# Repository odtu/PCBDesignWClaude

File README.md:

# PCBDesignWClaude: Inductive Absolute Encoder (branch `inductive-encoder`)

This branch holds a separate KiCad project from `main` (the 3-phase ESC): a contactless **absolute inductive rotary encoder**. It was designed with Claude Code and the PowerLab KiCad Assistant, after TI's **TIDA-010961** reference design ([TIDUFF8](https://www.ti.com/lit/pdf/tiduff8)).

- **Sensing:** dual-track Nonius coils, 16 and 15 periods, in a Ø58 mm coil area. The absolute angle comes from the phase difference between the two tracks.
- **Electronics:** 2 × LDC5072-Q1 inductive front ends, 2 × TLV9062 op-amps, an MSPM0G3507 MCU (both ADCs sample simultaneously) and a REF35330 3.3 V reference.
- **Power and interface:** 12–24 V input to an LMR51610 buck, then the TPS70950 and TPS70933 LDOs. The host connection carries UART at 2.5 Mbaud, SYNC and SWD.
- **Rules and parts:** the design follows the [METU PowerLab PCB design rules](https://github.com/odtu/Powerlab/blob/master/KiCAD/PCB_DESIGN_RULES.md) and uses parts from [PowerLabKiCadLibraries](https://github.com/odtu/PowerLabKiCadLibraries).

## Boards

The stack is the same as TI's: the target, a 0.5 mm air gap, the stator, then the 2×6 board-to-board headers, then the signal board.

| Board | Files | |
|---|---|---|
| Stator (coil board) | `InductiveEncoder.kicad_pro` | Ø76 mm, 4 layers. Generated coils, net ties, J2/J3 male headers on the bottom. No GND copper, so nothing acts as a shorted turn. |
| Signal board | `signal/EncoderSignal.kicad_pro` | Ø76 mm, 4 layers, the same M3 holes. All electronics. J2/J3 sockets on top, J1 host connector on the bottom. |
| Target | `target/EncoderTarget.kicad_pcb` | Ø56 mm, 2 layers, copper segments. It rotates with the shaft. |

## Status

- **Schematics:**
  - Hierarchical, on the PowerLab drawing sheet.
  - ERC: 0 errors.
  - PDFs: [docs/schematic_signal.pdf](docs/schematic_signal.pdf), [docs/schematic_stator.pdf](docs/schematic_stator.pdf).
- **Boards:**
  - DRC on both: 0 errors, 0 unconnected, 0 schematic-parity issues.
  - Remaining warnings: footprint-library mismatches (mask bridges allowed inside the fine-pitch ICs), one J1 silk circle near the edge, one narrow pour neck.
- **Fab outputs** in [fab/](fab/): Gerber and drill zip, BOM, position file and assembly drawings for each board.
- **Routing:**
  - The signal-board routing was reworked after [odtu/PowerLabKiCadAssistant#21](https://github.com/odtu/PowerLabKiCadAssistant/issues/21).
  - The resulting rules are proposed in odtu/Powerlab#147 and odtu/PowerLabKiCadAssistant#22. See "How the signal board was routed" below.

Before ordering:
- Add teardrops (Edit → Edit Teardrops; KiCad has no scripting API for them), then rerun `tools/fab_outputs.py`.
- Set the project number (`${PROJECTNUMBER}` is `TBD` in `tools/lab_setup.py`).
- Replace C4/C5 (22 µF 0603, 10 V) on the 6.1 V rail with 16–25 V parts. At 6.1 V they lose most of their capacitance to DC bias.
- The round boards need a panel for PCBWay assembly.
- There's no reverse-polarity protection: use a keyed cable.
- Firmware isn't part of this project.

## How the signal board was routed

`tools/route_signal.py` runs this chain on the placed board:

1. **`fanout.py`:**
   - **GND:** the pours connect the GND pads. A via goes at the pad only for decoupling caps and fine-pitch IC GND pins. Pads the pour can't reach got a via after routing.
   - **Fine-pitch power pins:** 0.25 mm neck-downs.
   - **Escape lanes:** kept free in front of fine-pitch pins.
2. **`power_route.py`:** the rails come first, at the 0.5 mm Power class width. Freerouting 2.4.1 ignores net-class widths.
3. **`autoroute.py signal`:** Freerouting 2.4.1 (Java 25) routes the signals. GND and the rails are keepouts, and the In1 GND plane is a plane layer.
4. **`maze_route.py`:** a grid A* router finishes what is still open. `ripup.py` frees a congested pin row first when needed.
5. **`track_opt.py`:**
   - Shortcuts detours with 45° segments and chamfers every corner of 90° or less.
   - Ends tracks straight at the pad centre.
   - Removes stubs and duplicates.
   - Widens Power/GND tracks to class width, with a 0.15 mm minimum for everything.

Afterwards, the finishing scripts add the rest:
- `zones.py signal`: the GND pours, slotted at 90° so they don't form a closed ring around the shaft;
- `lab_extras.py`: the stitching vias, the local fiducials at the MCU and the J1 labels;
- `silk.py` and `board_info.py`: the silkscreen and the board info.

The whole regeneration sequence, from coils and schematics to fab outputs, is in [docs/DESIGN_NOTES.md](docs/DESIGN_NOTES.md#regenerating).

## Repository layout

```
InductiveEncoder.kicad_*      stator project (root sheet + coils.kicad_sch)
signal/                       signal-board project (7 sheets)
target/                       target disc
tools/                        Python generators and layout/routing scripts (KiCad 10 python / system python)
fab/<board>/                  ordering files (Gerber+drill zip, BOM, pos, assembly PDFs)
docs/                         schematic PDFs, views, design notes
METUPowerLab_KiCadSchematicTemplate.kicad_wks   lab drawing sheet (also in signal/)
```

## Opening and regenerating

- **KiCad 10.**
  - The schematics and boards carry embedded copies of every symbol and footprint, so the project opens without extra libraries.
  - The new parts are in [odtu/PowerLabKiCadLibraries#13](https://github.com/odtu/PowerLabKiCadLibraries/pull/13): LDC5072, MSPM0G3507, TLV9062, REF35330, TPS709xx, the 2×6 header and socket, and some passives. That PR is not merged yet.
- **Generated files:** the `.kicad_sch` files are generated by `tools/encoder_circuit.py`, and the stator coils by `tools/coilgen.py`. Edit the scripts, not the generated sheets.
- **Tool paths:** some scripts have local paths you'll need to change on another machine:
  - the KiCad install, `C:/Program Files/KiCad/10.0`;
  - the PowerLab library and Assistant folders, used for logos, fiducials, Java 25 and Freerouting.

## License

See [license.txt](license.txt) (same as `main`).

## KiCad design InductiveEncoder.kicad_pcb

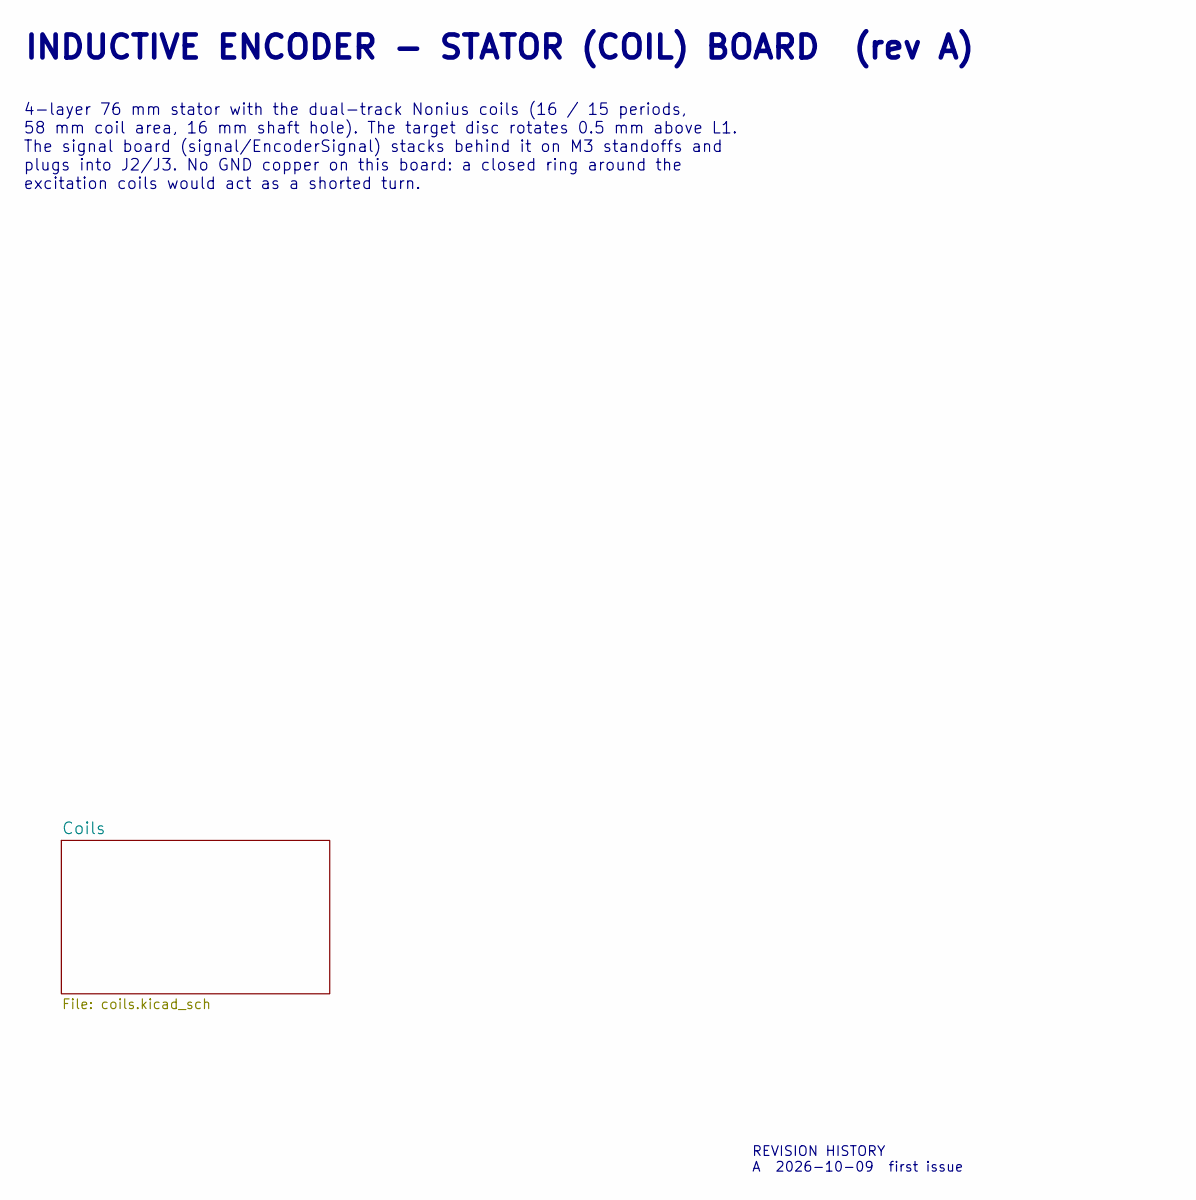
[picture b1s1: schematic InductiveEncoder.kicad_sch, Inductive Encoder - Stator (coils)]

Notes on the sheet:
INDUCTIVE ENCODER - STATOR (COIL) BOARD (rev A)
4-layer 76 mm stator with the dual-track Nonius coils (16 / 15 periods, 58 mm coil area, 16 mm shaft hole). The target disc rotates 0.5 mm above L1. The signal board (signal/EncoderSignal) stacks behind it on M3 standoffs and plugs into J2/J3. No GND copper on this board: a closed ring around the e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
REVISION HISTORY A 2026-10-09 first issue

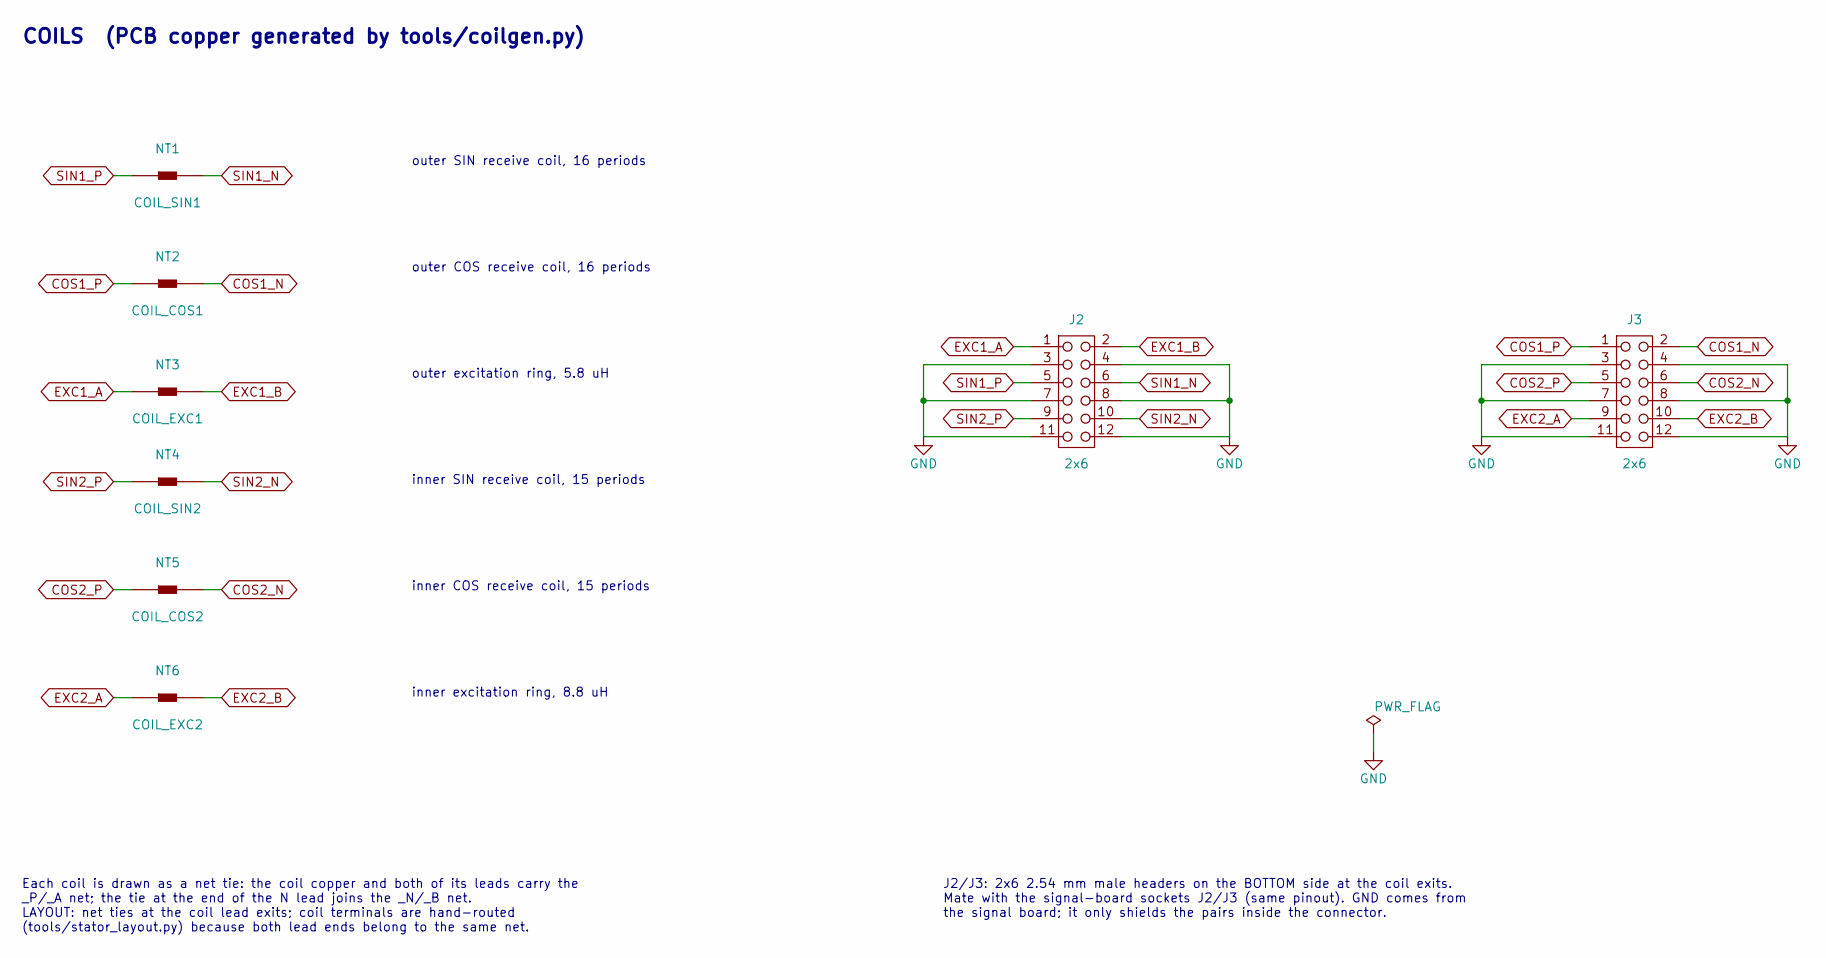
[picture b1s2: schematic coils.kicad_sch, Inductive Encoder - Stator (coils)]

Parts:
J2, J3: 2x6; 61301221121; Current Rating 3A; Voltage Rating 250V; Digi-Key Number 732-5297-ND
NT1: COIL_SIN1; NetTie_2_0.5mm
NT2: COIL_COS1; NetTie_2_0.5mm
NT3: COIL_EXC1; NetTie_2_0.5mm
NT4: COIL_SIN2; NetTie_2_0.5mm
NT5: COIL_COS2; NetTie_2_0.5mm
NT6: COIL_EXC2; NetTie_2_0.5mm

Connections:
COS1_N: J3.2, NT2.2
COS1_P: J3.1, NT2.1
COS2_N: J3.6, NT5.2
COS2_P: J3.5, NT5.1
EXC1_A: J2.1, NT3.1
EXC1_B: J2.2, NT3.2
EXC2_A: J3.9, NT6.1
EXC2_B: J3.10, NT6.2
GND: J2.3, J2.4, J2.7, J2.8, J2.11, J2.12, J3.3, J3.4, J3.7, J3.8, J3.11, J3.12
SIN1_N: J2.6, NT1.2
SIN1_P: J2.5, NT1.1
SIN2_N: J2.10, NT4.2
SIN2_P: J2.9, NT4.1

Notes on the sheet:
COILS (PCB copper generated by tools/coilgen.py)
outer SIN receive coil, 16 periods
outer COS receive coil, 16 periods
outer excitation ring, 5.8 uH
inner SIN receive coil, 15 periods
inner COS receive coil, 15 periods
inner excitation ring, 8.8 uH
Each coil is drawn as a net tie: the coil copper and both of its leads carry the _P/_A net; the tie at the end of the N lead joins the _N/_B net. LAYOUT: net ties at the coil lead exits; coil terminals are hand-routed (tools/stator_layout.py) because both lead ends belong to the same net.
J2/J3: 2x6 2.54 mm male headers on the BOTTOM side at the coil exits. Mate with the signal-board sockets J2/J3 (same pinout). GND comes from the signal board; it only shields the pairs inside the connector.

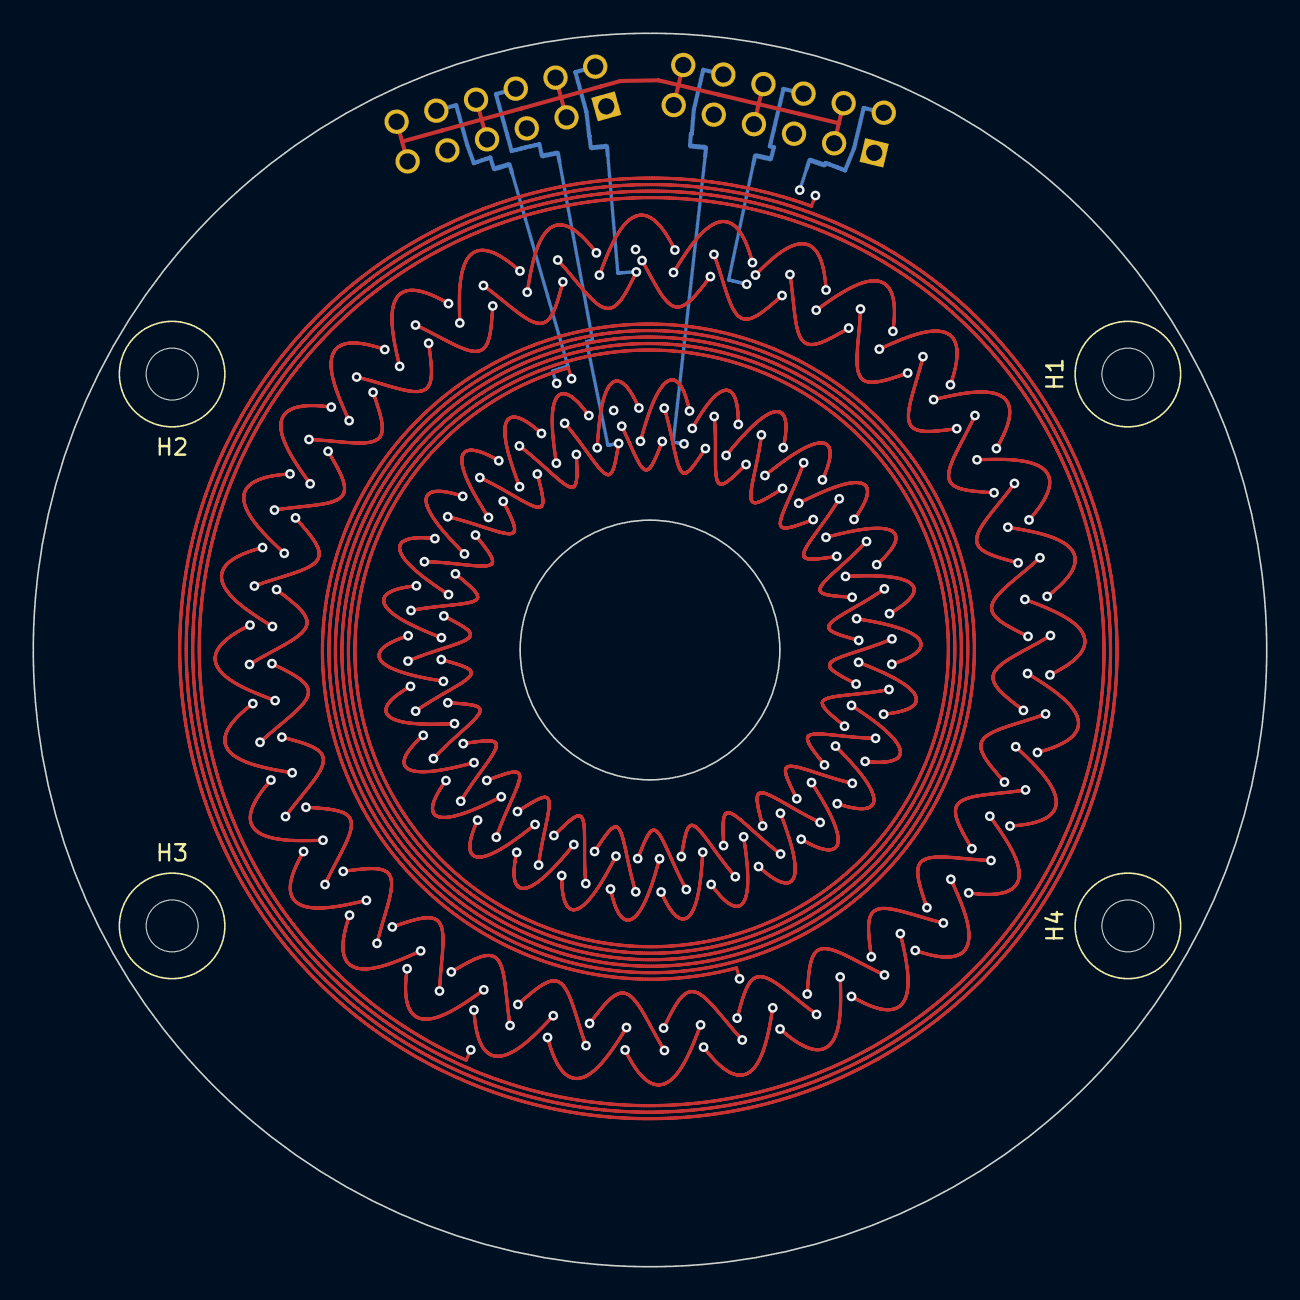
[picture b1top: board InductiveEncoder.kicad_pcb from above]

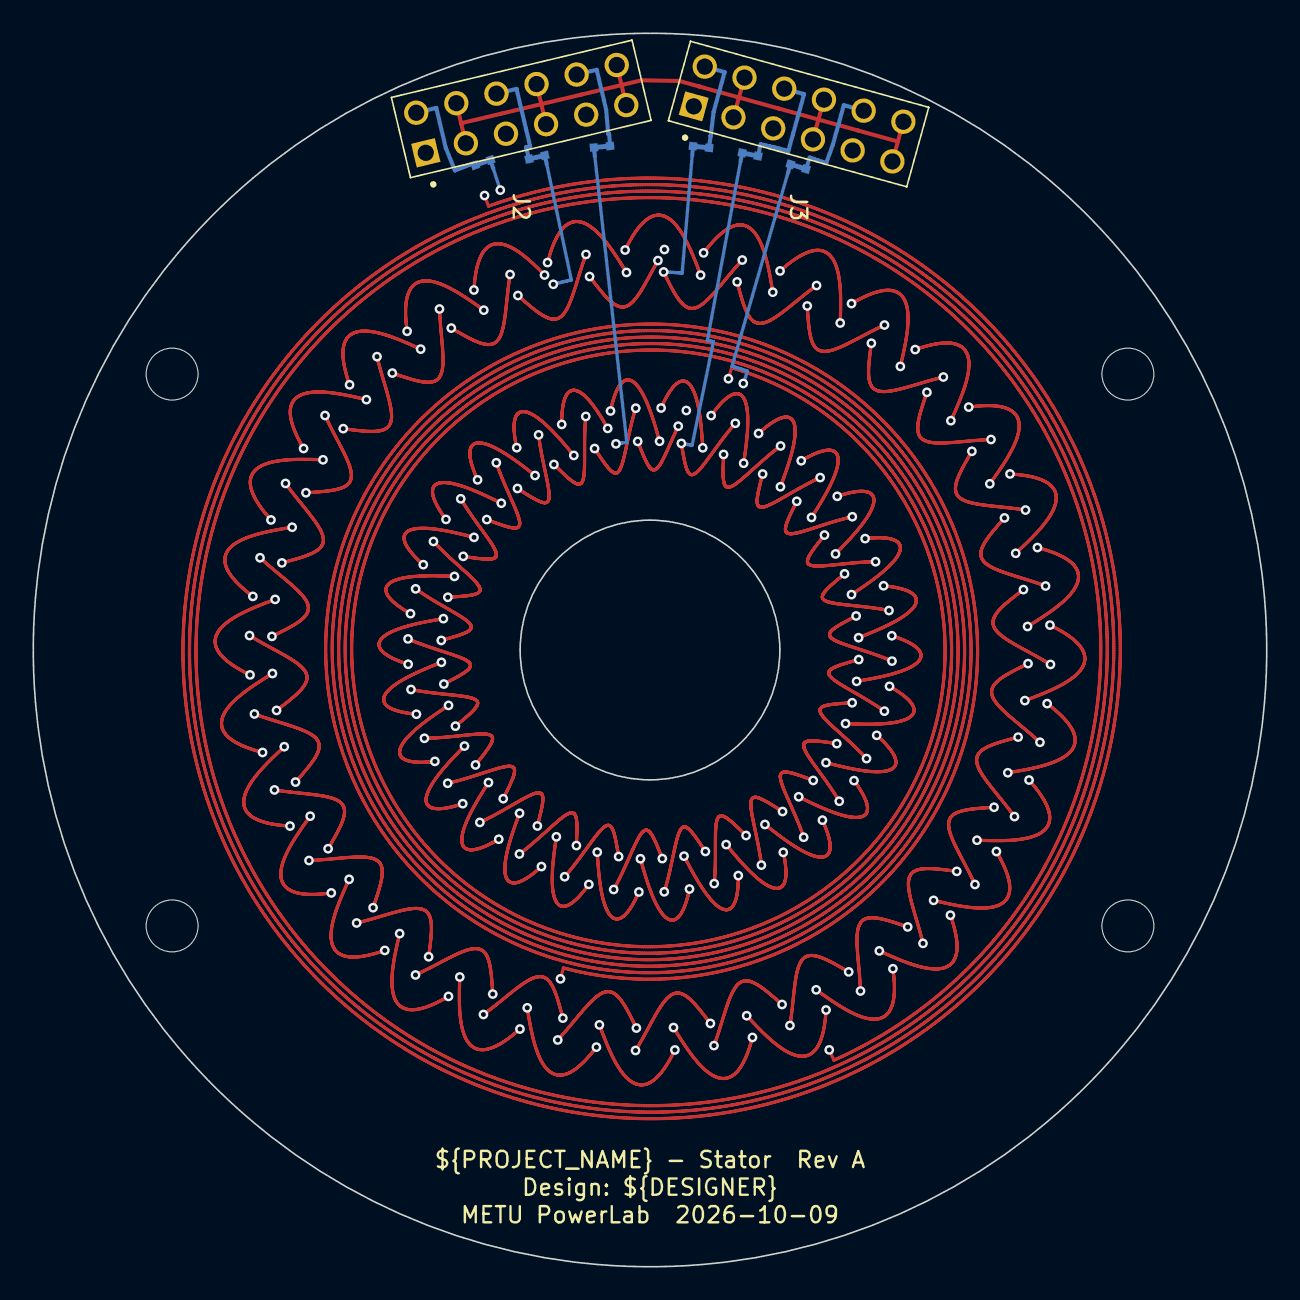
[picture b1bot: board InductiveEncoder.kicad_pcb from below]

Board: 4 copper layers, 76.0 x 76.0 mm, 12 parts (8 on the bottom side), 13 nets.

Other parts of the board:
H1, H2, H3, H4: M3_NPTH

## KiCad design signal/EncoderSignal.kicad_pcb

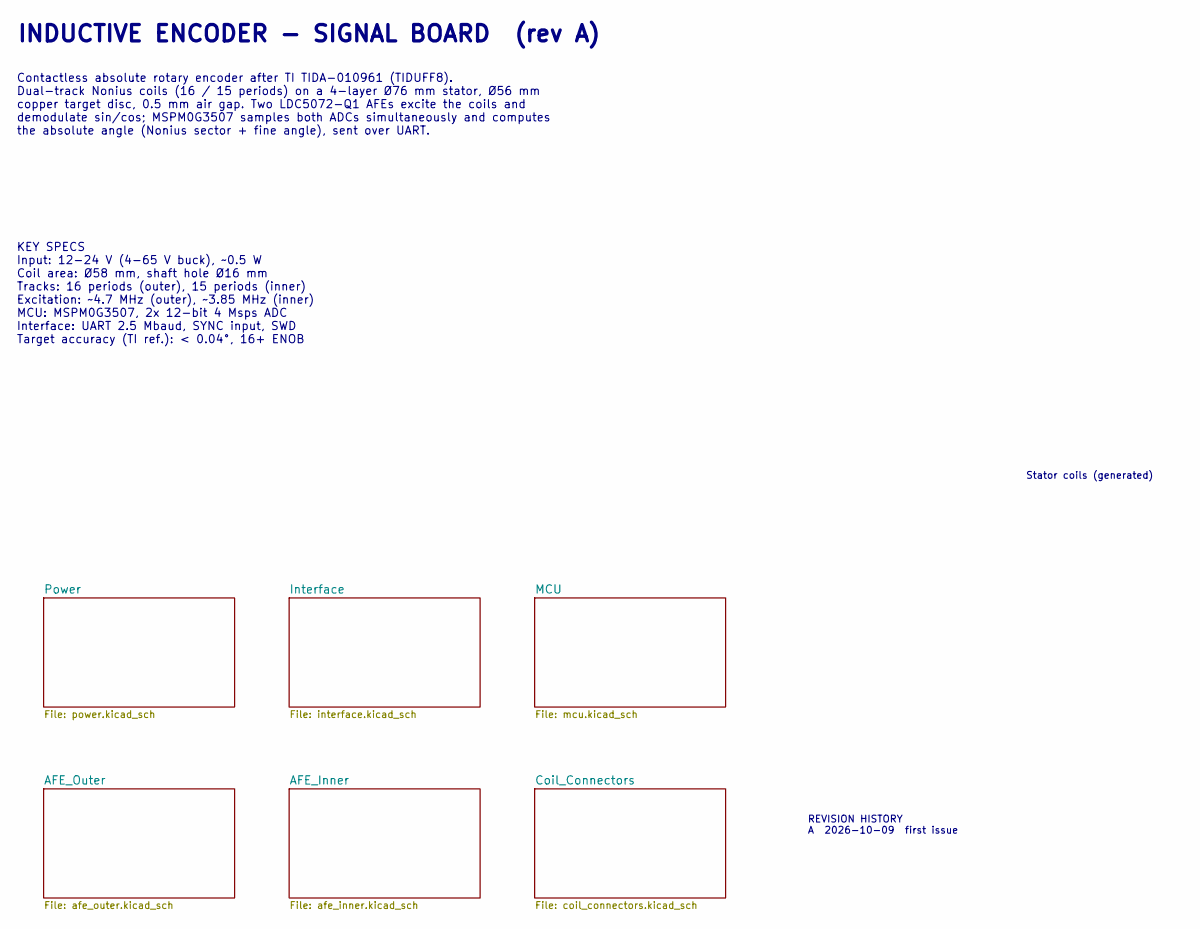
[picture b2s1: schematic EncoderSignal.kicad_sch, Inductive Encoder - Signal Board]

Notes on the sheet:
INDUCTIVE ENCODER - SIGNAL BOARD (rev A)
Contactless absolute rotary encoder after TI TIDA-010961 (TIDUFF8). Dual-track Nonius coils (16 / 15 periods) on a 4-layer Ø76 mm stator, Ø56 mm copper target disc, 0.5 mm air gap. Two LDC5072-Q1 AFEs excite the coils and demodulate sin/cos; MSPM0G3507 samples both ADCs simultaneously and computes 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
KEY SPECS Input: 12-24 V (4-65 V buck), ~0.5 W Coil area: Ø58 mm, shaft hole Ø16 mm Tracks: 16 periods (outer), 15 periods (inner) Excitation: ~4.7 MHz (outer), ~3.85 MHz (inner) MCU: MSPM0G3507, 2x 12-bit 4 Msps ADC Interface: UART 2.5 Mbaud, SYNC input, SWD Target accuracy (TI ref.): < 0.04°, 16+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
Stator coils (generated)
REVISION HISTORY A 2026-10-09 first issue

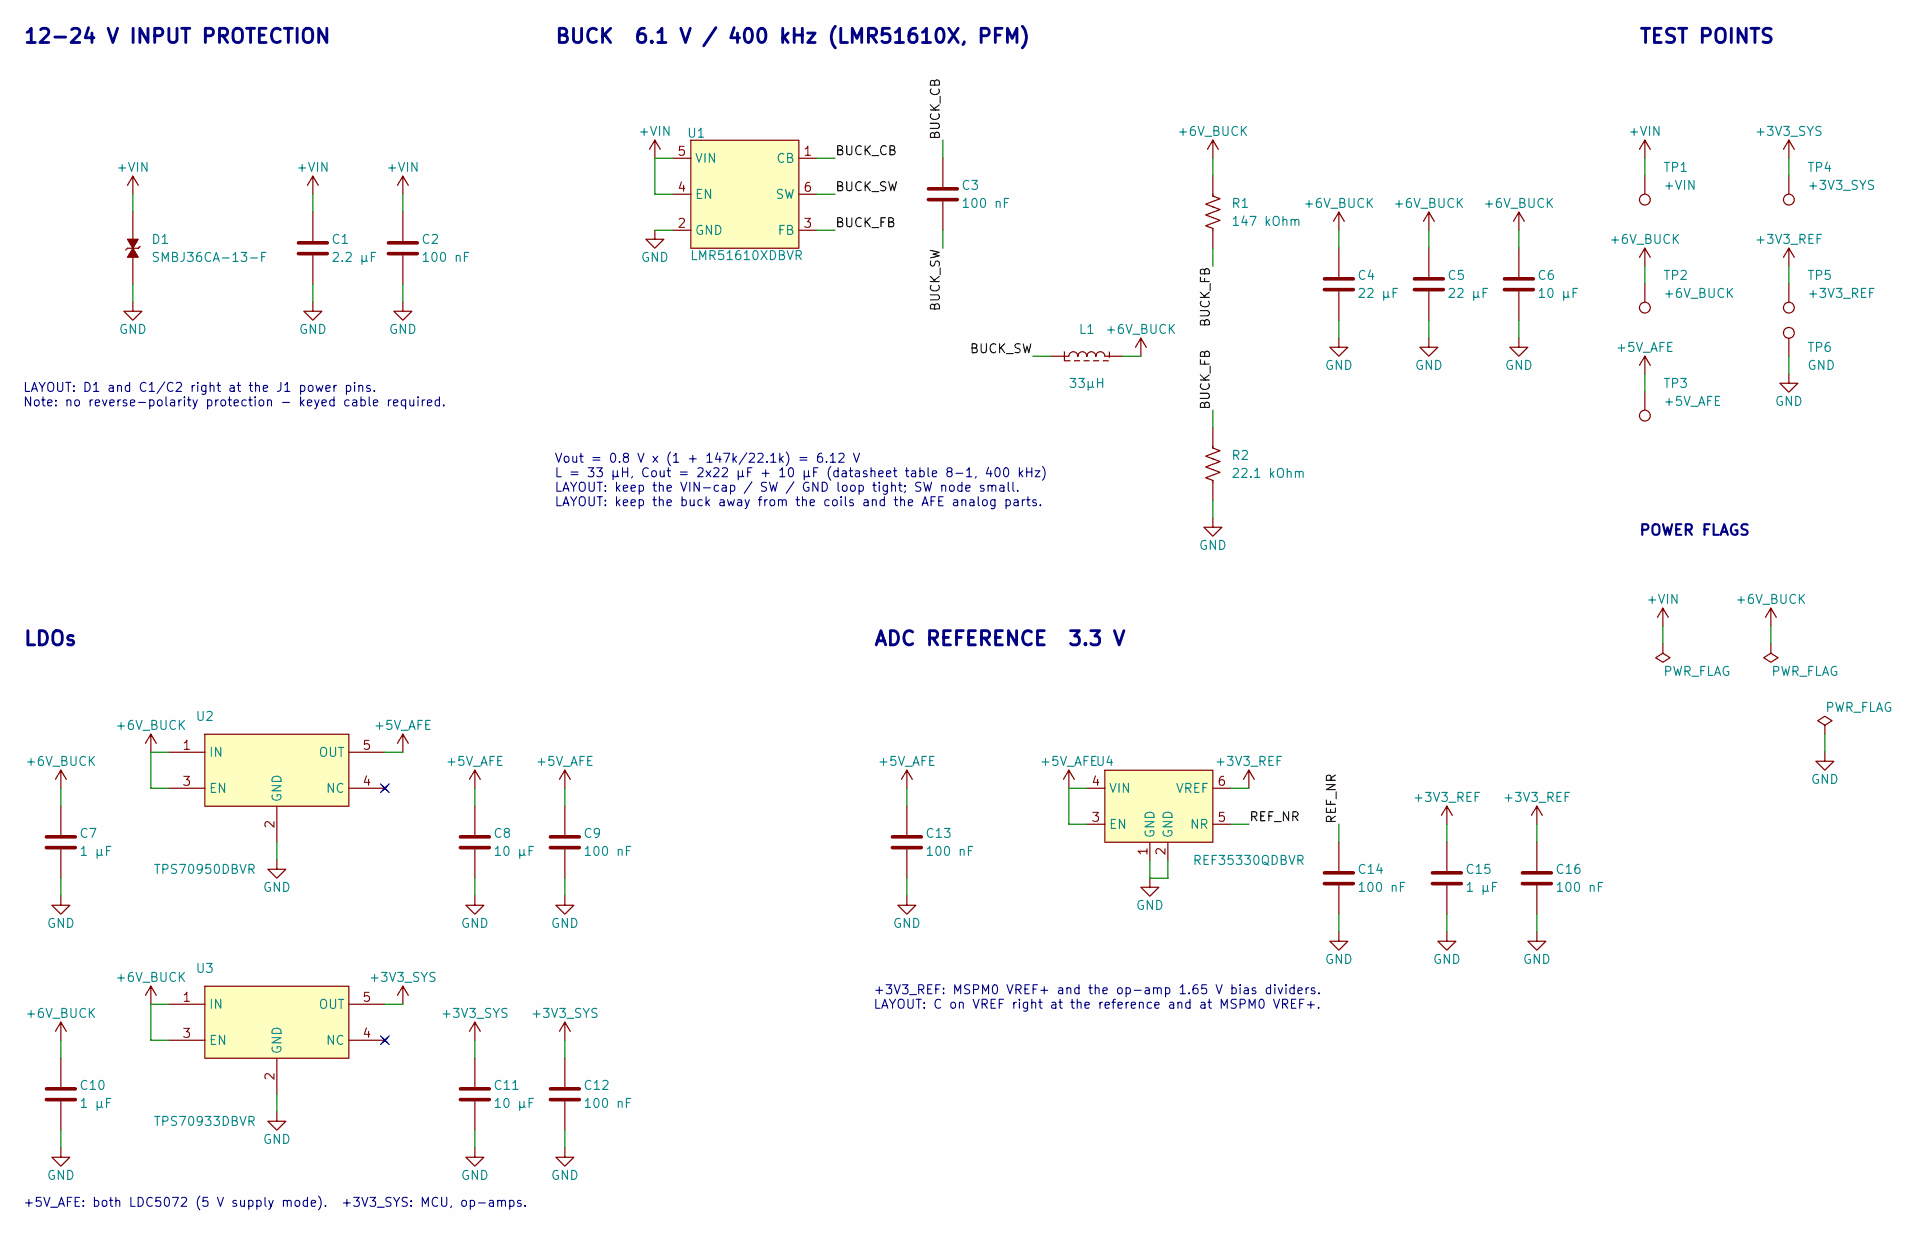
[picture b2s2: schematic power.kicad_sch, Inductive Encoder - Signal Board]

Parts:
C1: 2.2 µF; 0805_Medium; Tolerance ±20%; Voltage Rating 100V; Digi-Key Number 490-GRM21BD72A225ME01KCT-ND
C2: 100 nF; 0603_Medium; Tolerance ±10%; Voltage Rating 100V; Digi-Key Number 1276-6807-1-ND
C3, C9, C12, C13, C14, C16: 100 nF; 0603_Medium; Tolerance ±10%; Voltage Rating 16V; Digi-Key Number 311-1088-1-ND
C4, C5: 22 µF; 0603_Medium; Tolerance ±20%; Voltage Rating 10V; Digi-Key Number 1276-1274-1-ND
C6, C8, C11: 10 µF; 0603_Medium; Tolerance ±20%; Voltage Rating 25V; Digi-Key Number 1276-1869-1-ND
C7, C10, C15: 1 µF; 0603_Medium; Tolerance ±10%; Voltage Rating 10V; Digi-Key Number 1276-1946-1-ND
D1: SMBJ36CA-13-F; DO-214AA; Breakdown Voltage 40V; Clamping Voltage 58.1V; Digi-Key Number SMBJ36CA-FDICT-ND
L1: 33µH; 6x6mm; Tolerance ±20%; Current Rating 1.22A; Digi-Key Number 732-5537-1-ND
R1: 147 kOhm; 0603_Medium; Tolerance ±1%; Mouser Number 708-RMCF0603FT147K
R2: 22.1 kOhm; 0603_Medium; Tolerance ±1%; Mouser Number 708-RMCF0603FT22K1
TP1: +VIN; Pad_D1.5mm
TP2: +6V_BUCK; Pad_D1.5mm
TP3: +5V_AFE; Pad_D1.5mm
TP4: +3V3_SYS; Pad_D1.5mm
TP5: +3V3_REF; Pad_D1.5mm
TP6: GND; Pad_D1.5mm
U1: LMR51610XDBVR; SOT-23-6; Voltage Input Rating 4V up to 65V; Voltage Output Rating 0.8V up to 28V; Digi-Key Number 296-LMR51610XDBVRCT-ND
U2: TPS70950DBVR; SOT-23-5_DBV; Input Voltage (Max) 30V; Output Voltage 5V; Digi-Key Number 296-35484-1-ND
U3: TPS70933DBVR; SOT-23-5_DBV; Input Voltage (Max) 30V; Output Voltage 3.3V; Digi-Key Number 296-35483-1-ND
U4: REF35330QDBVR; SOT-23-6_DBV; Output Voltage 3.3V; Current Rating 10mA; Digi-Key Number 296-REF35330QDBVRCT-ND

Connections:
+3V3_REF: C15.1, C16.1, TP5.1, U4.6 (VREF); also elsewhere on the board
+3V3_SYS: C11.1, C12.1, TP4.1, U3.5 (OUT); also elsewhere on the board
+5V_AFE: C8.1, C9.1, C13.1, TP3.1, U2.5 (OUT), U4.3 (EN), U4.4 (VIN); also elsewhere on the board
+6V_BUCK: C4.1, C5.1, C6.1, C7.1, C10.1, L1.2, R1.1, TP2.1, U2.1 (IN), U2.3 (EN), U3.1 (IN), U3.3 (EN)
+VIN: C1.1, C2.1, D1.1, TP1.1, U1.4 (EN), U1.5 (VIN); also elsewhere on the board
/Power/BUCK_CB: C3.1, U1.1 (CB)
/Power/BUCK_FB: R1.2, R2.1, U1.3 (FB)
/Power/BUCK_SW: C3.2, L1.1, U1.6 (SW)
/Power/REF_NR: C14.1, U4.5 (NR)
GND: C1.2, C2.2, C4.2, C5.2, C6.2, C7.2, C8.2, C9.2, C10.2, C11.2, C12.2, C13.2, C14.2, C15.2, C16.2, D1.2, R2.2, TP6.1, U1.2 (GND), U2.2 (GND), U3.2 (GND), U4.1 (GND), U4.2 (GND); also elsewhere on the board

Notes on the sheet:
12-24 V INPUT PROTECTION
LAYOUT: D1 and C1/C2 right at the J1 power pins. Note: no reverse-polarity protection - keyed cable required.
BUCK 6.1 V / 400 kHz (LMR51610X, PFM)
Vout = 0.8 V x (1 + 147k/22.1k) = 6.12 V L = 33 µH, Cout = 2x22 µF + 10 µF (datasheet table 8-1, 400 kHz) LAYOUT: keep the VIN-cap / SW / GND loop tight; SW node small. LAYOUT: keep the buck away from the coils and the AFE analog parts.
LDOs
+5V_AFE: both LDC5072 (5 V supply mode). +3V3_SYS: MCU, op-amps.
ADC REFERENCE 3.3 V
+3V3_REF: MSPM0 VREF+ and the op-amp 1.65 V bias dividers. LAYOUT: C on VREF right at the reference and at MSPM0 VREF+.
TEST POINTS
POWER FLAGS

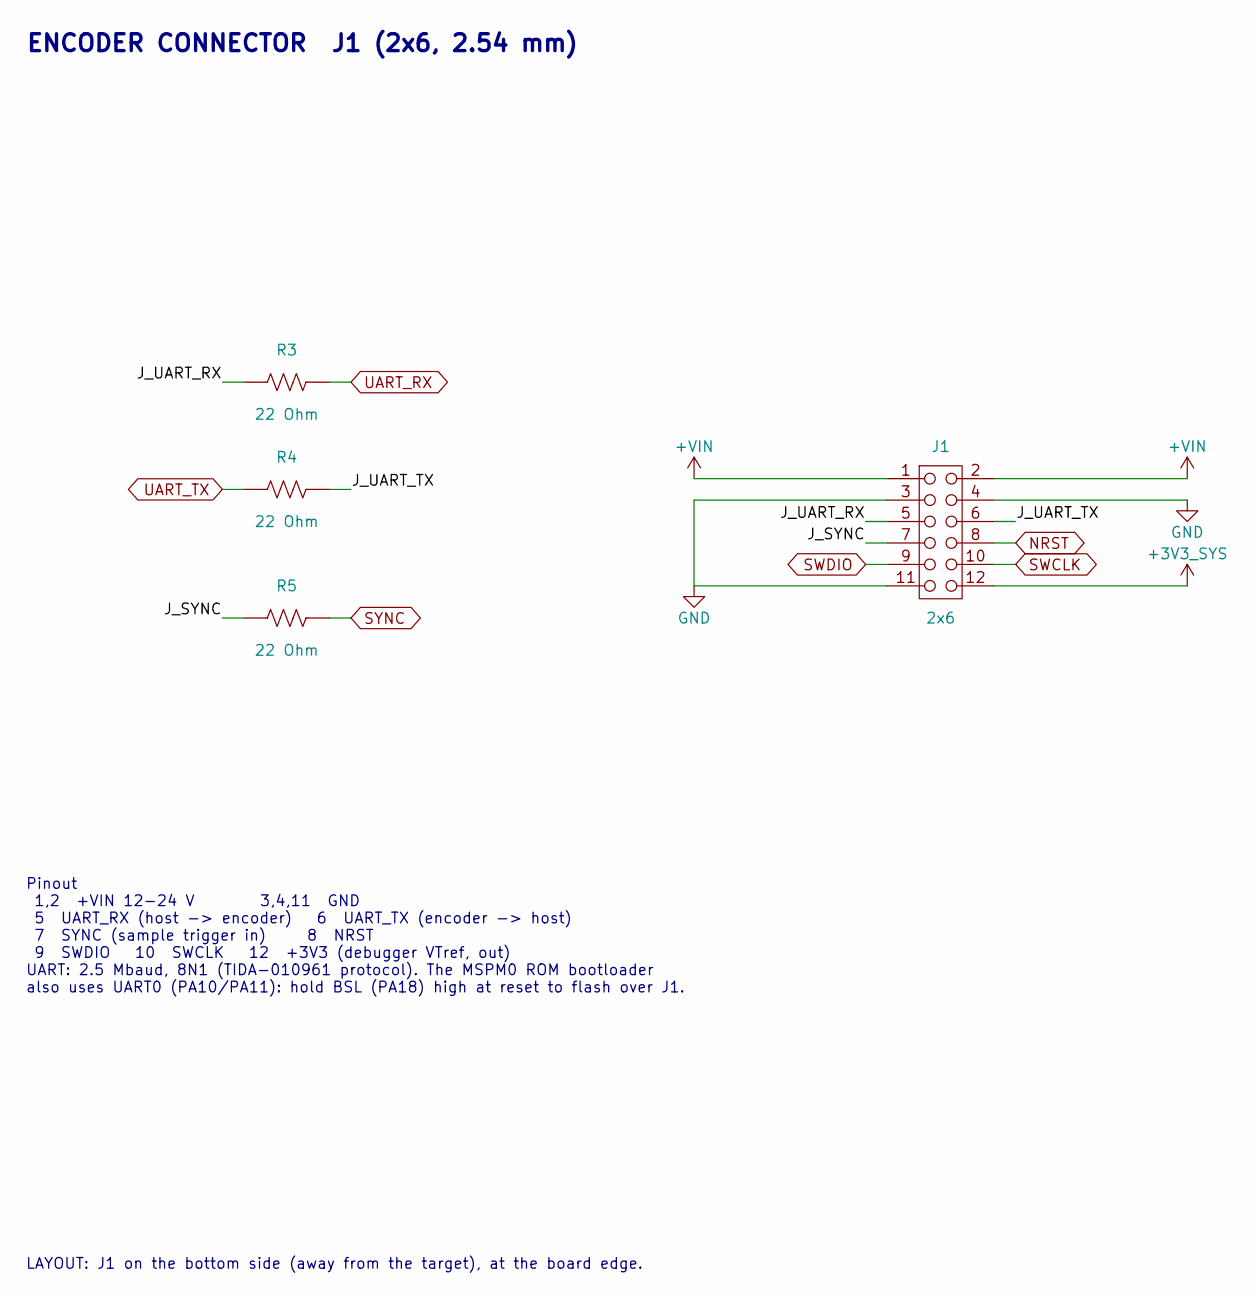
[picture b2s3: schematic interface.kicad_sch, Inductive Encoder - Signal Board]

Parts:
J1: 2x6; 61301221121; Current Rating 3A; Voltage Rating 250V; Digi-Key Number 732-5297-ND
R3, R4, R5: 22 Ohm; 0603_Medium; Tolerance ±1%; Mouser Number 708-RMCF0603FT22R0

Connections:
+3V3_SYS: J1.12; also elsewhere on the board
+VIN: J1.1, J1.2; also elsewhere on the board
/Interface/J_SYNC: J1.7, R5.1
/Interface/J_UART_RX: J1.5, R3.1
/Interface/J_UART_TX: J1.6, R4.2
GND: J1.3, J1.4, J1.11; also elsewhere on the board
NRST: J1.8; also elsewhere on the board
SWCLK: J1.10; also elsewhere on the board
SWDIO: J1.9; also elsewhere on the board
SYNC: R5.2; also elsewhere on the board
UART_RX: R3.2; also elsewhere on the board
UART_TX: R4.1; also elsewhere on the board

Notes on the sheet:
ENCODER CONNECTOR J1 (2x6, 2.54 mm)
Pinout 1,2 +VIN 12-24 V 3,4,11 GND 5 UART_RX (host -> encoder) 6 UART_TX (encoder -> host) 7 SYNC (sample trigger in) 8 NRST 9 SWDIO 10 SWCLK 12 +3V3 (debugger VTref, out) UART: 2.5 Mbaud, 8N1 (TIDA-010961 protocol). The MSPM0 ROM bootloader also uses UART0 (PA10/PA11): hold BSL (PA18) high at rese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
LAYOUT: J1 on the bottom side (away from the target), at the board edge.

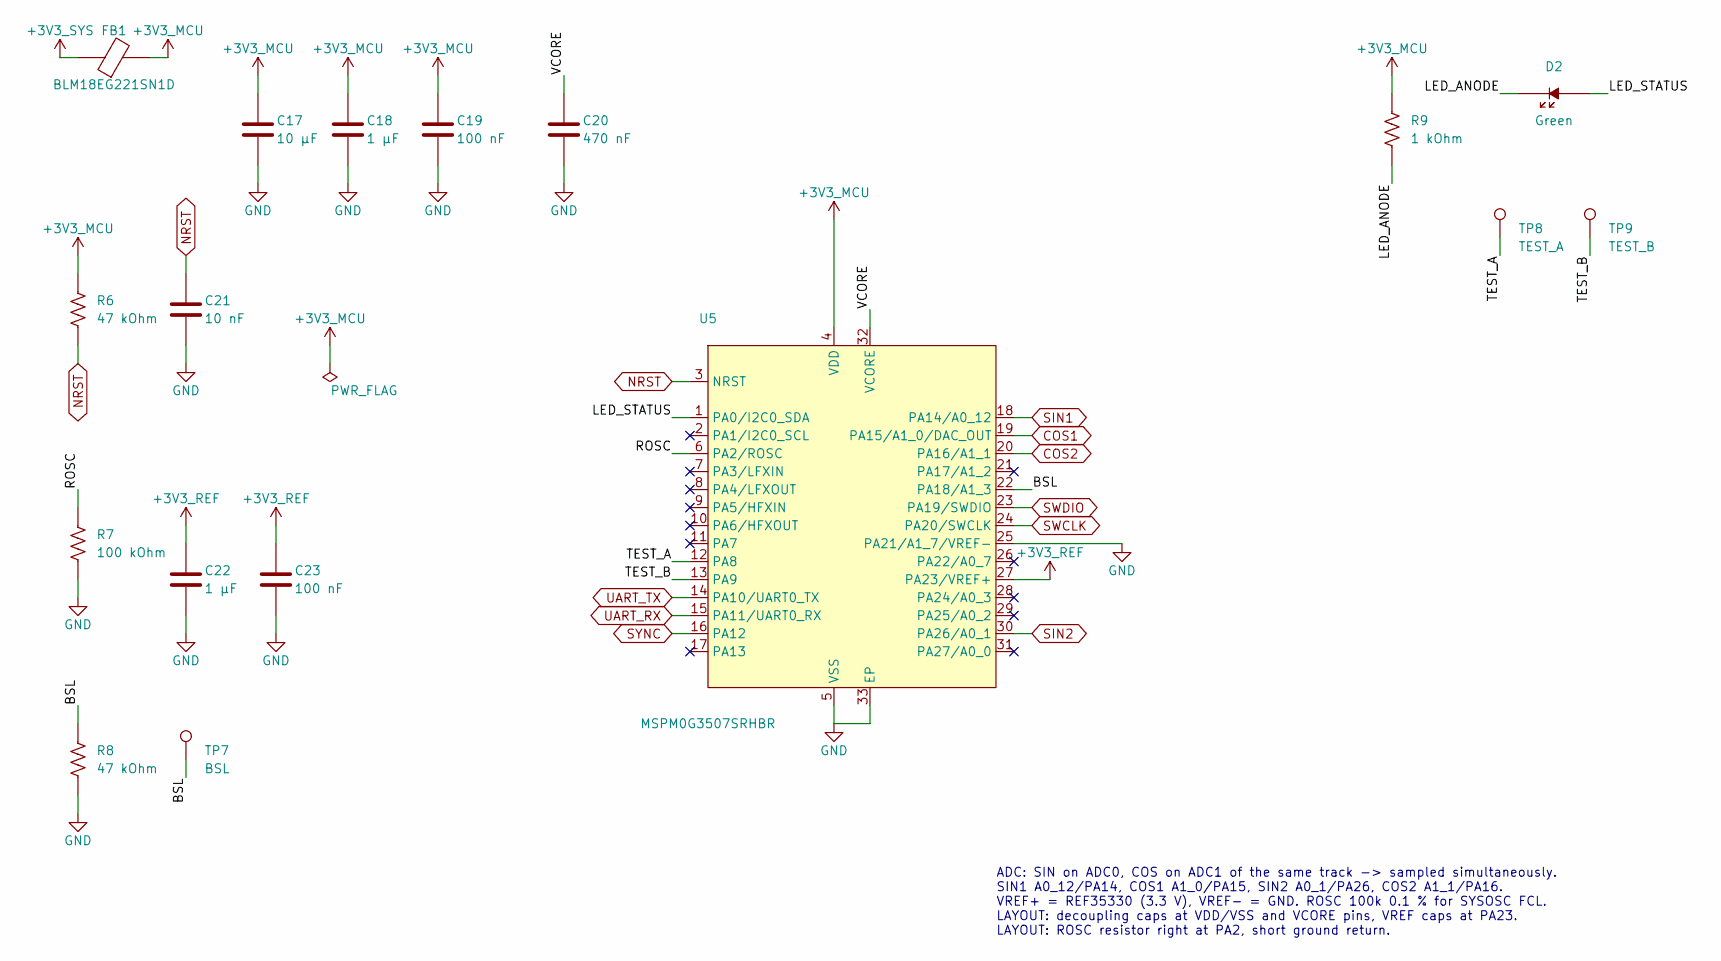
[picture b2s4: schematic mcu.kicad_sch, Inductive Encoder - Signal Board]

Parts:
C17: 10 µF; 0603_Medium; Tolerance ±20%; Voltage Rating 25V; Digi-Key Number 1276-1869-1-ND
C18, C22: 1 µF; 0603_Medium; Tolerance ±10%; Voltage Rating 10V; Digi-Key Number 1276-1946-1-ND
C19, C23: 100 nF; 0603_Medium; Tolerance ±10%; Voltage Rating 16V; Digi-Key Number 311-1088-1-ND
C20: 470 nF; 0603_Medium; Tolerance ±10%; Voltage Rating 25V; Digi-Key Number 490-3291-1-ND
C21: 10 nF; 0603_Medium; Tolerance ±10%; Voltage Rating 50V; Digi-Key Number 1276-1009-1-ND
D2: Green; 0603_Medium; Forward Voltage 3.2V; Current Rating 20mA; Digi-Key Number 732-4971-1-ND
FB1: BLM18EG221SN1D; 0603_Medium; Current Rating 2A; Digi-Key Number 490-3992-1-ND
R6, R8: 47 kOhm; 0603_Medium; Tolerance ±1%; Mouser Number 708-RMCF0603FT47K0
R7: 100 kOhm; 0603_Medium; Tolerance 0.1%; Mouser Number 603-RT0603BRD07100KL
R9: 1 kOhm; 0603_Medium; Tolerance ±1%; Mouser Number 708-RMCF0603FT1K00
TP7: BSL; Pad_D1.5mm
TP8: TEST_A; Pad_D1.5mm
TP9: TEST_B; Pad_D1.5mm
U5: MSPM0G3507SRHBR; VQFN-32_RHB; Supply Voltage Range 1.62V up to 3.6V; Digi-Key Number 296-MSPM0G3507SRHBRCT-ND

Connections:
+3V3_MCU: C17.1, C18.1, C19.1, FB1.2, R6.1, R9.1, U5.4 (VDD)
+3V3_REF: C22.1, C23.1, U5.27 (PA23/VREF+); also elsewhere on the board
+3V3_SYS: FB1.1; also elsewhere on the board
/MCU/BSL: R8.1, TP7.1, U5.22 (PA18/A1_3)
/MCU/LED_ANODE: D2.2, R9.2
/MCU/LED_STATUS: D2.1, U5.1 (PA0/I2C0_SDA)
/MCU/ROSC: R7.1, U5.6 (PA2/ROSC)
/MCU/TEST_A: TP8.1, U5.12 (PA8)
/MCU/TEST_B: TP9.1, U5.13 (PA9)
/MCU/VCORE: C20.1, U5.32 (VCORE)
COS1: U5.19 (PA15/A1_0/DAC_OUT); also elsewhere on the board
COS2: U5.20 (PA16/A1_1); also elsewhere on the board
GND: C17.2, C18.2, C19.2, C20.2, C21.2, C22.2, C23.2, R7.2, R8.2, U5.5 (VSS), U5.25 (PA21/A1_7/VREF-), U5.33 (EP); also elsewhere on the board
NRST: C21.1, R6.2, U5.3 (NRST); also elsewhere on the board
SIN1: U5.18 (PA14/A0_12); also elsewhere on the board
SIN2: U5.30 (PA26/A0_1); also elsewhere on the board
SWCLK: U5.24 (PA20/SWCLK); also elsewhere on the board
SWDIO: U5.23 (PA19/SWDIO); also elsewhere on the board
SYNC: U5.16 (PA12); also elsewhere on the board
UART_RX: U5.15 (PA11/UART0_RX); also elsewhere on the board
UART_TX: U5.14 (PA10/UART0_TX); also elsewhere on the board

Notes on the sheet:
ADC: SIN on ADC0, COS on ADC1 of the same track -> sampled simultaneously. SIN1 A0_12/PA14, COS1 A1_0/PA15, SIN2 A0_1/PA26, COS2 A1_1/PA16. VREF+ = REF35330 (3.3 V), VREF- = GND. ROSC 100k 0.1 % for SYSOSC FCL. LAYOUT: decoupling caps at VDD/VSS and VCORE pins, VREF caps at PA23. LAYOUT: ROSC resis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
